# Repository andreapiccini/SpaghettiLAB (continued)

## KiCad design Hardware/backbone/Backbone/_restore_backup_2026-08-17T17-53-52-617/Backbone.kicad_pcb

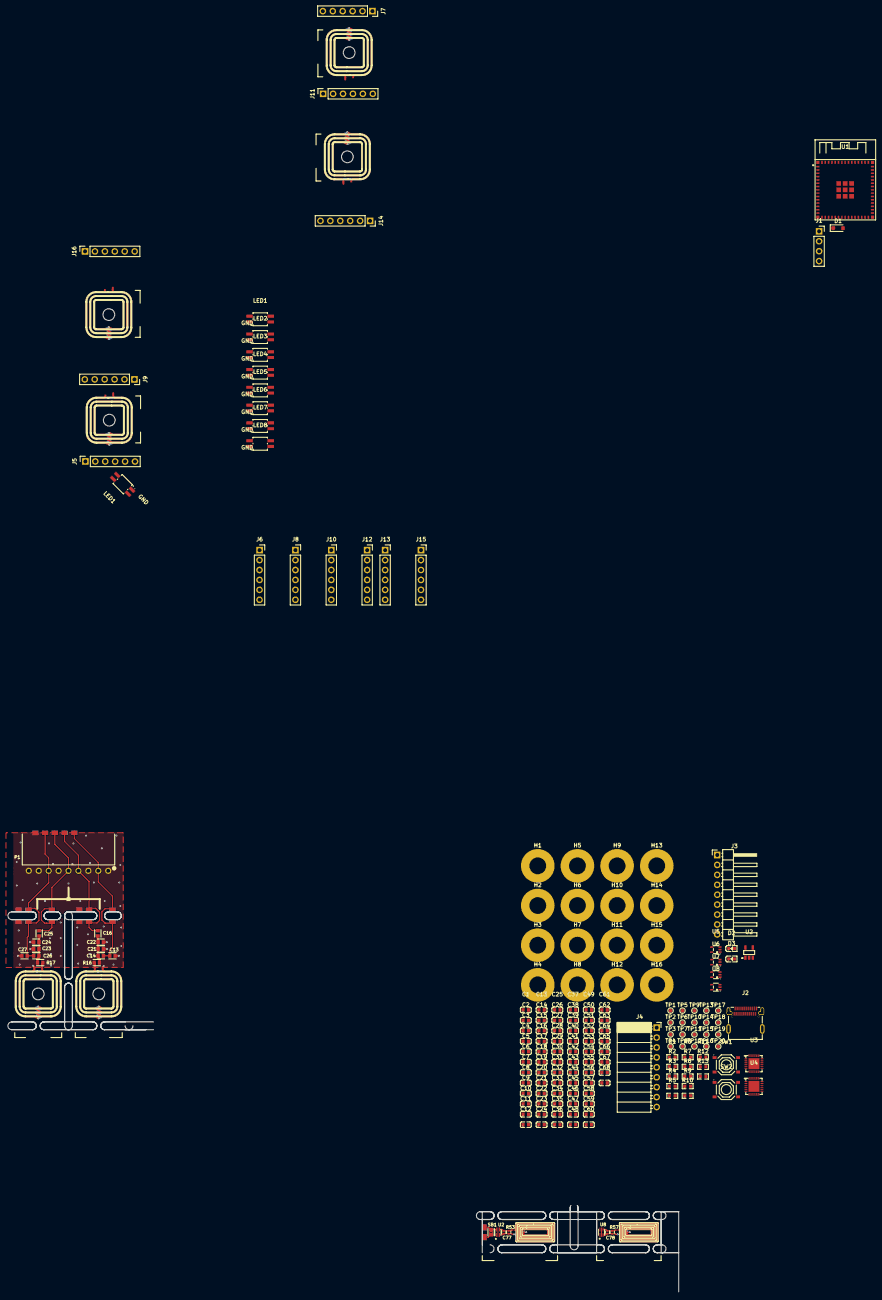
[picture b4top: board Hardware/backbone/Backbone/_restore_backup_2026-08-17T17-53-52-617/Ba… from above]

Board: 2 copper layers, 179 parts (0 on the bottom side), 118 nets.

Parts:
C1, C2, C9, C10, C25, C26#2, C39, C40, C41, C42, C47, C48, C53, C54, C67, C68: 100nF; C0603
C3, C8: 1uF; C0603
C4, C5, C6, C7, C56, C59, C62, C65: 10pF; C0603
C11, C12, C15, C16, C17, C18, C23#2, C24#2, C31, C32, C33, C34: 10nF; C0603
C13, C14, C19, C20, C21#2, C22#2, C35, C36: 2.2uF/10V; C0603
C13#2, C27: 150pF; 0603
C14#2, C26: 10pF; 0603
C16#2, C25#2: 39pF 2%; 0603
C21, C24: 220pF; 0603
C22, C23: 18pF 2%; 0603
C27#2, C28, C37, C38: 1uF/10V; C0603
C29, C30: 4.7uF/10V; C0603
C43, C44, C45, C46: 220pF 1%; C0603
C49, C50, C51, C52: 33pF 2%; C0603
C55, C58, C63, C66: 240pF; C0603
C57, C60, C61, C64: 150pF; C0603
C77: 33pF; 0402
C78: 6.8pF; 0402
D1: D_Schottky; D_SOD-323_HandSoldering
D2, D3: LED; LED0603-RD
H1, H2, H3, H4, H5, H6, H7, H8, H9, H10, H11, H12, H13, H14, H15, H16: Magnet; MountingHole_4.3mm_M4_Pad
J1: PROG; PinSocket_1x04_P2.54mm_Vertical
J2: USB_C_Receptacle_USB2.0_14P; USB-C-SMD_TYPEC-324G-BCP24
J3: EXP_MALE; PinHeader_1x09_P2.54mm_Horizontal
J4: EXP_FEMALE; PinSocket_1x09_P2.54mm_Horizontal
J5, J6, J7, J8, J9, J10, J11, J12, J13, J14, J15, J16: Conn_01x06_Socket; PinSocket_1x06_P2.54mm_Vertical
LED1, LED1#2, LED2, LED3, LED4, LED5, LED6, LED7, LED8: SK6812MINI-E; LED-SMD_4P-L3.2-W2.8-LS5.9_SK6812MINI-E
NT_C7_1, NT_C7_2: Net-Tie-Width-0.50mm; Net-Tie-WIDTH-0.50mm
NT_TAG1, NT_TAG2: Net-Tie-Width-0.10mm; Net-Tie-WIDTH-0.10mm
P1: SSW-109-02-G-S-RA; SAMTEC-SSW-1X9PTS-RA-THROUGH-HOLE
R1: 4.7k; R0603
R2, R3: 33R; R0603
R4, R5: 10k; R0603
R6, R7: 5.1k; R0603
R8, R9: 330R; R0603
R10, R11, R12, R13: 1R5; R0603
R16, R17: 1R5; 0603
R53, R57: TBD; 0402
SB1: SB 0603; STRAP-FORMAT-0603-OUVERT
SW1: RESET; SW-SMD_4P-L5.1-W5.1-P3.70-LS6.5-TL_H1.5
SW2: BOOT; SW-SMD_4P-L5.1-W5.1-P3.70-LS6.5-TL_H1.5
TP1, TP2, TP3, TP4, TP5, TP6, TP7, TP8, TP9, TP10, TP11, TP12: SMD/0.6mm; TestPoint_Pad_D1.0mm
TP13, TP14, TP15, TP16, TP17, TP18, TP19, TP20: SMD/0.8mm; TestPoint_Pad_D1.0mm
U1: ESP32-S3-MINI-1; BULETM-SMD_ESP32-S3-MINI-1-N8
U2: AP2112K-3.3TRG1; SOT-25-5_L2.9-W1.6-P0.95-LS2.8-BL
U2#2: ST25TV02KC-TFH3; ST-UFDFPN5-Pas=0.4-PKG-1.7x1.4
U3, U4: ST25R200; QFN-24_L4.0-W4.0-P0.50-TL-EP2.8
U5, U6, U7, U8#2: SN74AHCT1G14DCKR; SOT-353_L2.2-W1.4-P0.65-LS2.4-BR
U8: ST25TN01KAFH5; ST-UFDFPN5-Pas=0.4-PKG-1.7x1.4

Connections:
5V: C8.2, C25.2, C26#2.2 (2_2), C37.2, C38.2, C39.2, C40.2, C41.2, C42.2, C47.2, C48.2, C53.2, C54.2, C67.2, C68.2, D1.1 (K), J3.2, J4.8, J13.6, J14.6, J15.6, J16.6, LED1.3 (VDD), LED2.3 (VDD), LED3.3 (VDD), LED4.3 (VDD), LED5.3 (VDD), LED6.3 (VDD), LED7.3 (VDD), LED8.3 (VDD), R9.1, U2.1 (VIN), U2.3 (EN), U5.5 (VCC), U6.5 (VCC), U7.5 (VCC), U8#2.5 (VCC)
/AGD: C27#2.2, C28.2, C33.2, C34.2, U3.15 (AGD), U4.15 (AGD)
/BAY0: U1.19 (IO15), U6.2 (A)
/BAY1: U1.20 (IO16), U7.2 (A)
/BAY2: U1.21 (IO17), U5.2 (A)
/BAY3: U1.22 (IO18), U8#2.2 (A)
/RFI1_25R200: C56.1, C57.2, C59.1, C60.2, U3.16 (RFI1), U4.16 (RFI1)
/RFI2_25R200: C61.1, C62.2, C64.1, C65.2, U3.17 (RFI2), U4.17 (RFI2)
/RFO1_25R200: TP18.1 (1_1), TP20.1 (1_1), U3.9 (RFO1), U4.9 (RFO1)
/RFO1_C7_ANT: C44.1, C46.1, C49.1, C50.1
/RFO2_25R200: TP17.1 (1_1), TP19.1 (1_1), U3.10 (RFO2), U4.10 (RFO2)
/RFO2_C7_ANT: C43.2, C45.2, C51.1, C52.1
/TAD1_200: TP13.1 (1_1), TP14.1 (1_1), U3.13 (TAD1), U4.13 (TAD1)
/TAD2_200: TP15.1 (1_1), TP16.1 (1_1), U3.12 (TDA2), U4.12 (TDA2)
/USB_DM: R3.1, U1.23 (USB_D-)
/USB_DP: R2.1, U1.24 (USB_D+)
/VDD_A: C17.2, C18.2, C21#2.2, C22#2.2, U3.14 (VDD_A), U4.14 (VDD_A)
/VDD_AM: C15.2, C16.2, C19.2, C20.2, U3.6 (VDD_AM), U4.6 (VDD_AM)
/VDD_D: C11.2, C12.2, C13.2, C14.2, U3.5 (VDD_D), U4.5 (VDD_D)
/VDD_DR: C31.2, C32.2, C35.2, C36.2, U3.8 (VDD_DR), U4.8 (VDD_DR)
/XTI: C4.2, C6.2, U3.19 (XTI), U4.19 (XTI)
/XTO: C5.2, C7.2, U3.20 (XTO), U4.20 (XTO)
GND: C1.1, C2.1, C3.1, C4.1, C5.1, C6.1, C7.1, C8.1, C9.1, C10.1, C11.1, C12.1, C13.1, C14.1, C15.1, C16.1, C17.1, C18.1, C19.1, C20.1, C21#2.1, C22#2.1, C23#2.1, C24#2.1, C25.1, C27#2.1, C28.1, C29.1, C30.1, C31.1, C32.1, C33.1, C34.1, C35.1, C36.1, C37.1, C38.1, C39.1, C40.1, C41.1, C42.1, C43.1, C44.2, C45.1, C46.2, C47.1, C48.1, C53.1, C54.1, C55.2, C57.1, C58.2, C60.1, C61.2, C63.1, C64.2, C66.1, C67.1, C68.1, D2.1 (K), D3.1 (K), J1.4, J2.A1 (GND), J2.A12 (GND), J2.B1 (GND), J2.B12 (GND), J3.9, J4.1, J13.1, J14.1, J15.1, J16.1, LED1.1 (GND), LED2.1 (GND), LED3.1 (GND), LED4.1 (GND), LED5.1 (GND), LED6.1 (GND), LED7.1 (GND), LED8.1 (GND), R6.1, R7.1, SW1.1, SW2.1, U1.1 (GND), U1.2 (GND), U1.42 (GND), U1.43 (GND), U1.46 (GND), U1.47 (GND), U1.48 (GND), U1.49 (GND), U1.50 (GND), U1.51 (GND), U1.52 (GND), U1.53 (GND), U1.54 (GND), U1.55 (GND), U1.56 (GND), U1.57 (GND), U1.58 (GND), U1.59 (GND), U1.60 (GND), U2.2 (GND), U3.4 (GND_D), U3.11 (GND_DR), U3.18 (GND_A), U3.25 (GND(EP)), U4.4 (GND_D), U4.11 (GND_DR), U4.18 (GND_A), U4.25 (GND(EP)), U5.3 (GND), U6.3 (GND), U7.3 (GND), U8#2.3 (GND)
GND_HUB: C13#2.2, C21.1, C22.1, C23.2, C24.2, C27.1, NT_C7_1.1, NT_C7_2.1, P1.1, P1.3, P1.6, P1.8, P1.9
IO1: J16.5, U1.5 (IO1)
IO2: J16.4, U1.6 (IO2)
IO3: J16.3, U1.7 (IO3)
IO4: J16.2, U1.8 (IO4)
IO5: J15.5, U1.9 (IO5)
IO6: J15.4, U1.10 (IO6)
IO7: J15.3, U1.11 (IO7)
IO8: J15.2, U1.12 (IO8)
IO9: J14.5, U1.13 (IO9)
IO10: J14.4, U1.14 (IO10)
IO11: J14.3, U1.15 (IO11)
IO12: J14.2, U1.16 (IO12)
IO13: J13.5, U1.17 (IO13)
IO14: J13.4, U1.18 (IO14)
IO21: J13.3, U1.25 (IO21)
IO26: J13.2, U1.26 (IO26)
IO33: R5.2, TP6.1 (1_1), U1.28 (IO33), U4.22 (BSS)
IO34: TP11.1 (1_1), TP12.1 (1_1), U1.29 (IO34), U3.2 (MISO), U4.2 (MISO)
IO35: TP7.1 (1_1), U1.31 (IO35), U3.1 (IRQ)
IO36: TP3.1 (1_1), TP4.1 (1_1), U1.32 (IO36), U3.24 (SCLK), U4.24 (SCLK)
IO37: TP9.1 (1_1), TP10.1 (1_1), U1.33 (IO37), U3.23 (MOSI), U4.23 (MOSI)
IO38: R4.2, TP5.1 (1_1), U1.34 (IO38), U3.22 (BSS)
IO39: TP1.1 (1_1), TP2.1 (1_1), U1.35 (IO39), U3.21 (RESET), U4.21 (RESET)
IO40: TP8.1 (1_1), U1.36 (IO40), U4.1 (IRQ)
IO41: J3.3, J4.7, U1.37 (IO41)
IO42: J3.4, J4.6, U1.38 (IO42)
IO45: J3.5, J4.5, U1.41 (IO45)
IO46: J3.6, J4.4, U1.44 (IO46)
IO47: J3.7, J4.3, U1.27 (IO47)
IO48: J3.8, J4.2, U1.30 (IO48)
unnamed: C49.2, C55.1, C56.2, R10.1
unnamed: C50.2, C58.1, C59.2, R11.1
unnamed: C51.2, C62.1, C63.2, R12.1
unnamed: C52.2, C65.1, C66.2, R13.1
unnamed: D2.2 (A), R8.2
unnamed: D3.2 (A), R9.2
unnamed: J1.2, U1.39 (TXD0)
unnamed: J1.3, U1.40 (RXD0)
unnamed: J2.A5 (CC1), R7.2
unnamed: J2.B5 (CC2), R6.2
unnamed: J2.A6 (D+), J2.B6 (D+), R2.2
unnamed: J2.A7 (D-), J2.B7 (D-), R3.2
unnamed: J5.1, J9.6
unnamed: J5.2, J9.5
unnamed: J5.3, J9.4
unnamed: J5.4, J9.3
unnamed: J5.5, J9.2
unnamed: J5.6, J9.1
unnamed: J6.6, J10.1
unnamed: J6.5, J10.2
unnamed: J6.4, J10.3
unnamed: J6.3, J10.4
unnamed: J6.2, J10.5
unnamed: J6.1, J10.6
unnamed: J7.6, J11.1
unnamed: J7.5, J11.2
unnamed: J7.4, J11.3
unnamed: J7.3, J11.4
unnamed: J7.2, J11.5
unnamed: J7.1, J11.6
unnamed: J8.6, J12.1
unnamed: J8.5, J12.2
unnamed: J8.4, J12.3
unnamed: J8.3, J12.4
unnamed: J8.2, J12.5
unnamed: J8.1, J12.6
unnamed: LED1.2 (DIN), U5.4 (Y)
unnamed: LED1.4 (DOUT), LED3.2 (DIN)
unnamed: LED2.2 (DIN), U6.4 (Y)
unnamed: LED2.4 (DOUT), LED4.2 (DIN)
unnamed: LED5.2 (DIN), U7.4 (Y)
unnamed: LED5.4 (DOUT), LED7.2 (DIN)
unnamed: LED6.2 (DIN), U8#2.4 (Y)
unnamed: LED6.4 (DOUT), LED8.2 (DIN)
unnamed: R1.2, SW1.2, U1.45 (EN)
unnamed: SW2.2, U1.4 (IO0)
unnamed: C23#2.2, C29.2, U3.7 (VDD)
unnamed: C24#2.2, C30.2, U4.7 (VDD)
NetC14_1: C14#2.1, C16#2.2, C21.2, C22.2, R16.1
NetC23_1: C23.1, C24.1, C25#2.2, C26.2, R17.1
NetC77_1: C77.1, NT_TAG1.1, R53.1, U2#2.4
NetC77_2: C77.2, NT_TAG1.2, R53.2, U2#2.3
NetC78_1: C78.1, NT_TAG2.1, R57.1, U8.4
NetC78_2: C78.2, NT_TAG2.2, R57.2, U8.3
NetNT_C7_1_2: NT_C7_1.2, R17.2
NetNT_C7_2_2: NT_C7_2.2, R16.2
NetSB1_1: SB1.1, U2#2.5
NetSB1_2: SB1.2, U2#2.1
RFI1_C7_ANT: C26.1, C27.2, P1.7
RFI2_C7_ANT: C13#2.1, C14#2.2, P1.2
RFO1_C7_ANT: C25#2.1, P1.5
RFO2_C7_ANT: C16#2.1, P1.4
VBUS: D1.2 (A), J2.A4 (VBUS), J2.A9 (VBUS), J2.B4 (VBUS), J2.B9 (VBUS)
VCORE: C1.2, C2.2, C3.2, C9.2, C10.2, J1.1, J3.1, J4.9, R1.1, R4.1, R5.1, R8.1, U1.3 (3V3), U2.5 (VOUT), U3.3 (VDD_IO), U4.3 (VDD_IO)

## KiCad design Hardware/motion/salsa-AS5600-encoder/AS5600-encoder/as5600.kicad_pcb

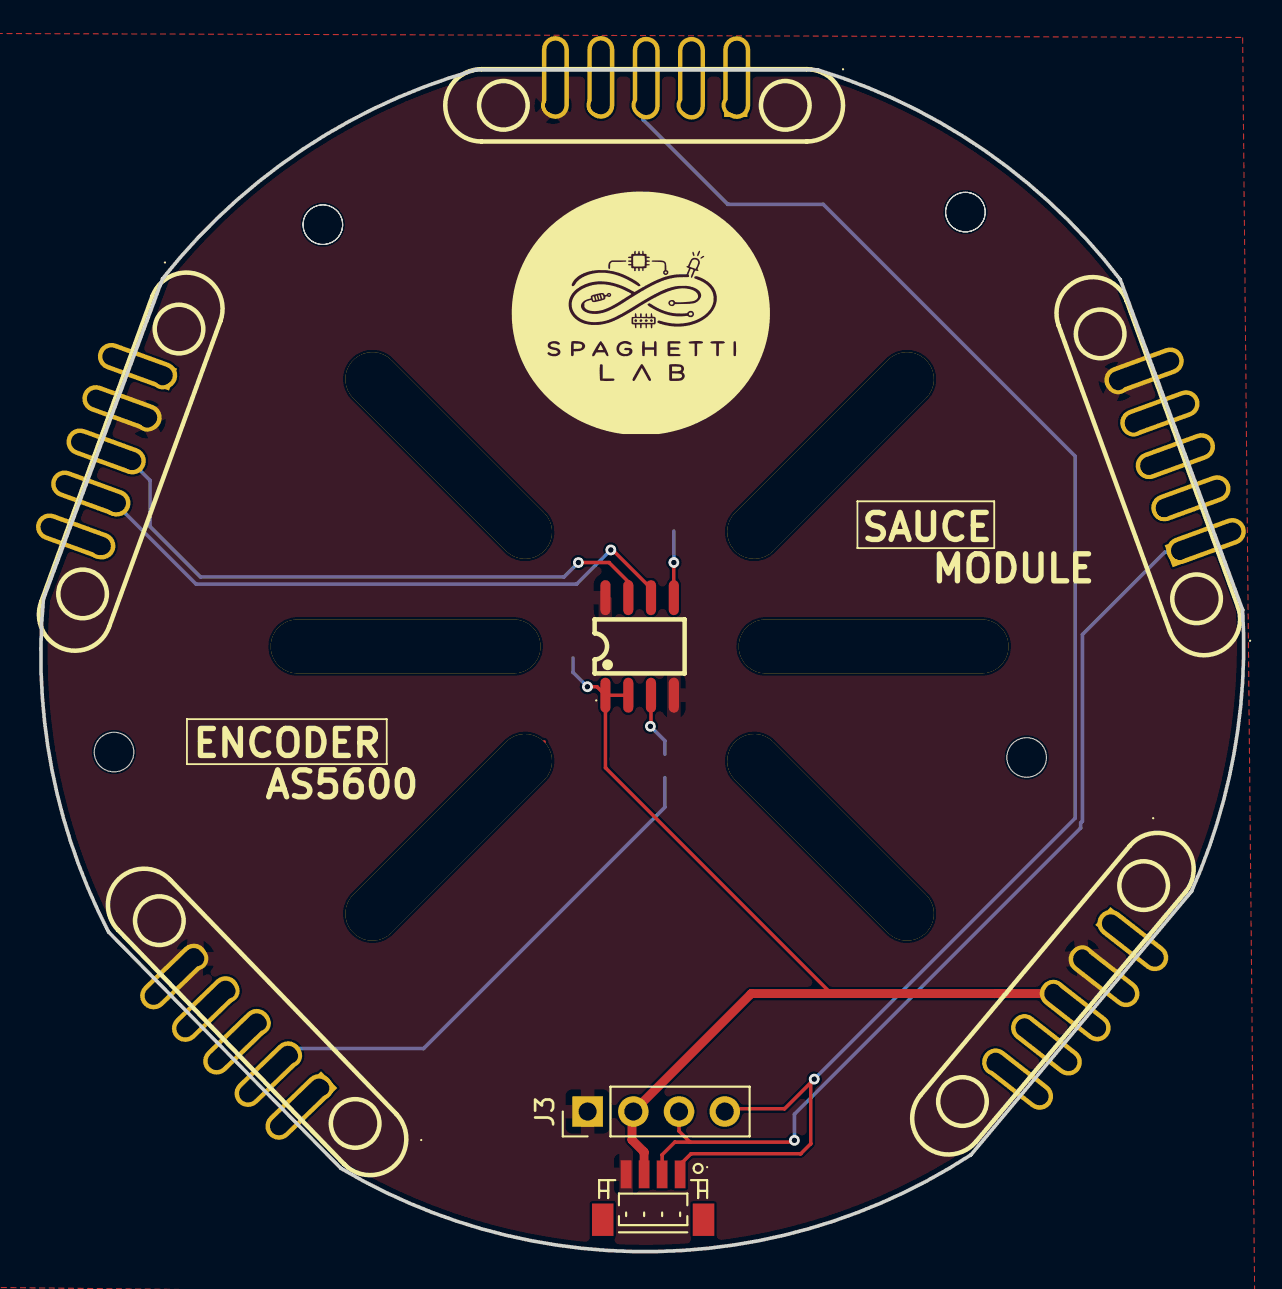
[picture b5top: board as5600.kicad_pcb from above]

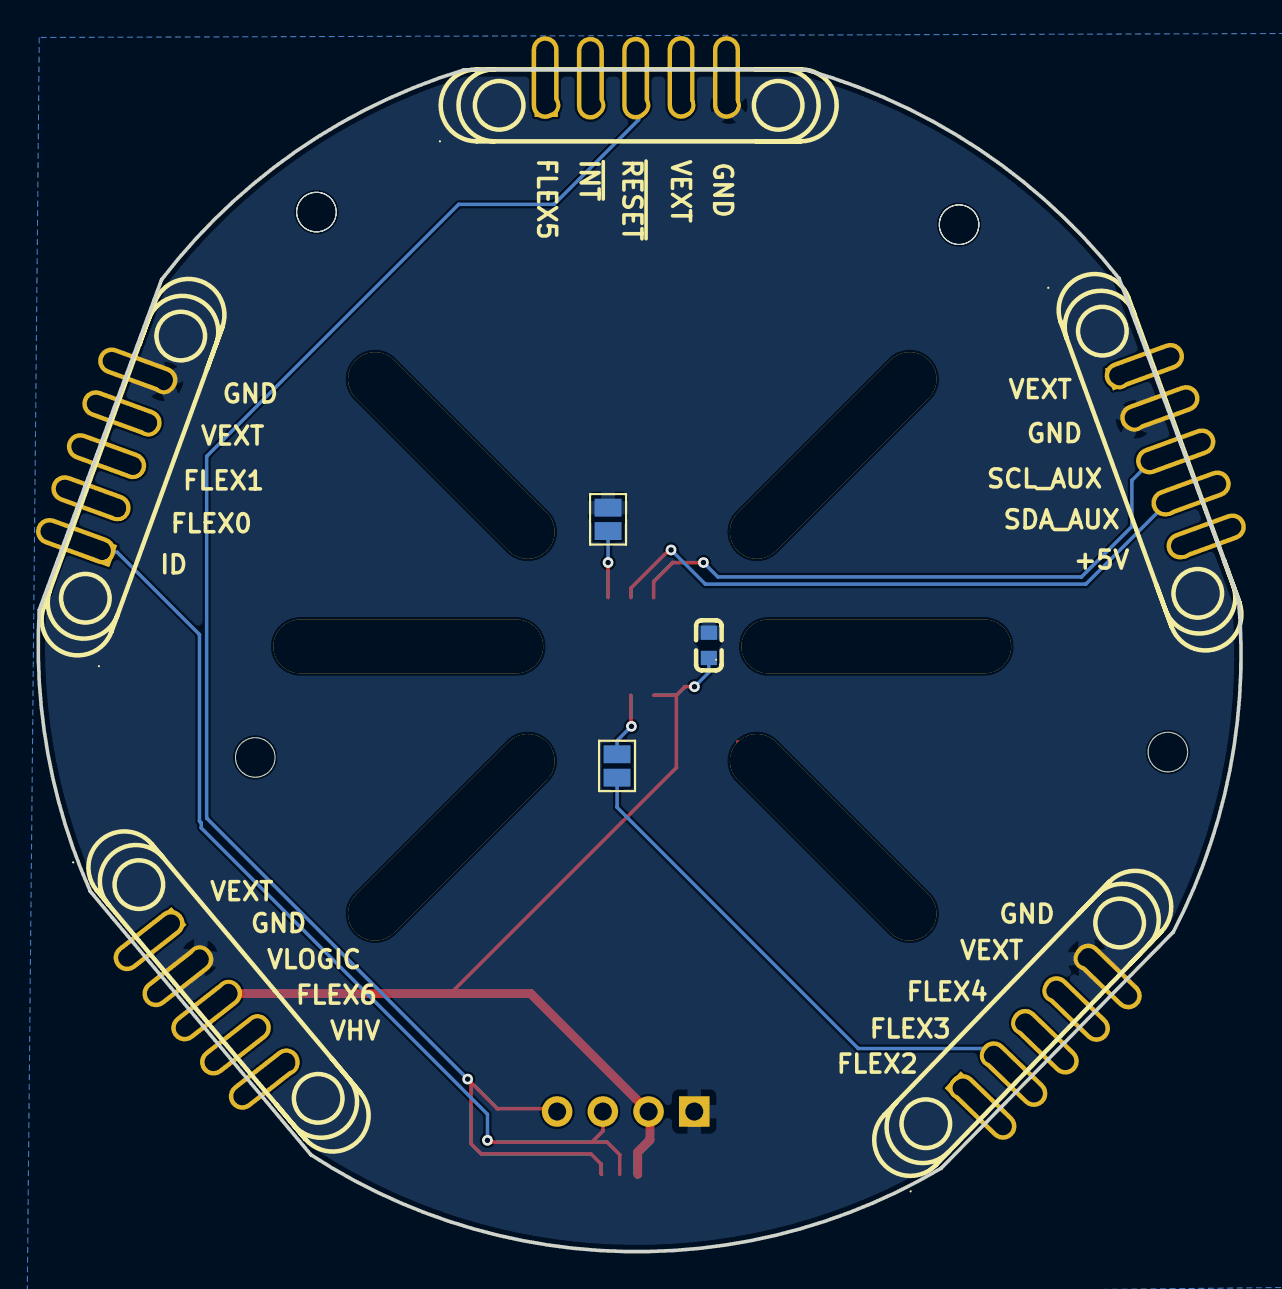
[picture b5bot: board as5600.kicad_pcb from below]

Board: 2 copper layers, 66.8 x 65.6 mm, 22 parts (8 on the bottom side), 19 nets.

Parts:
C1: 100nF 10V; C0603
CN7, CN8, CN9, CN10, CN11: PR5L4015-5P-C-F; CONN-TH_PR5L4015-5P-C-F
H1, H2, H3, H3#2, H4, H4#2: MountingHole; MountingHole_2.2mm_M2
J1: Conn_01x04_Socket; CONN-SMD_BM04B-SRSS-TB
J3: Conn_01x04_Pin; PinHeader_1x04_P2.54mm_Vertical
JP2, JP4: ENC_PGO; SolderJumper-2_P1.3mm_Open_Pad1.0x1.5mm
U1: AS5600-ASOT; SOIC-8_L5.0-W4.0-P1.27-LS6.0-BL
U35, U36, U37, U38, U39: PR5L5015-5P-C-H; CONN-TH_PR5L5015-5P-C-H

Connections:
5V: CN8.5, U35.5
+3.3V: C1.1, CN11.3, J1.3, J3.2, U1.1 (VDD5V), U1.2 (VDD3V3), U39.3
/FLEX0: CN10.2, U37.2
/FLEX1: CN10.3, U37.3
/FLEX2: CN7.1, U38.1
/FLEX3: CN7.2, JP4.2 (B), U38.2
/FLEX4: CN7.3, U38.3
/FLEX5: CN9.1, U36.1
/FLEX6: CN11.4, U39.4
/ID: CN10.1, J1.2, J3.3, U37.1
/~INT: CN9.2, U36.2
/~RESET: CN9.3, J1.1, J3.4, U36.3
ENC_AOUT: JP4.1 (A), U1.3 (OUT)
ENC_SCL: CN8.3, U1.7 (SCL), U35.3
ENC_SDA: CN8.4, U1.6 (SDA), U35.4
GND: C1.2, CN7.5, CN8.2, CN9.5, CN10.5, CN11.2, J1.4, J3.1, JP2.2 (B), U1.4 (GND), U1.8 (DIR), U35.2, U36.5, U37.5, U38.5, U39.2
unnamed: JP2.1 (A), U1.5 (PGO)
VEXT: CN7.4, CN8.1, CN9.4, CN10.4, CN11.1, U35.1, U36.4, U37.4, U38.4, U39.1
VHV: CN11.5, U39.5

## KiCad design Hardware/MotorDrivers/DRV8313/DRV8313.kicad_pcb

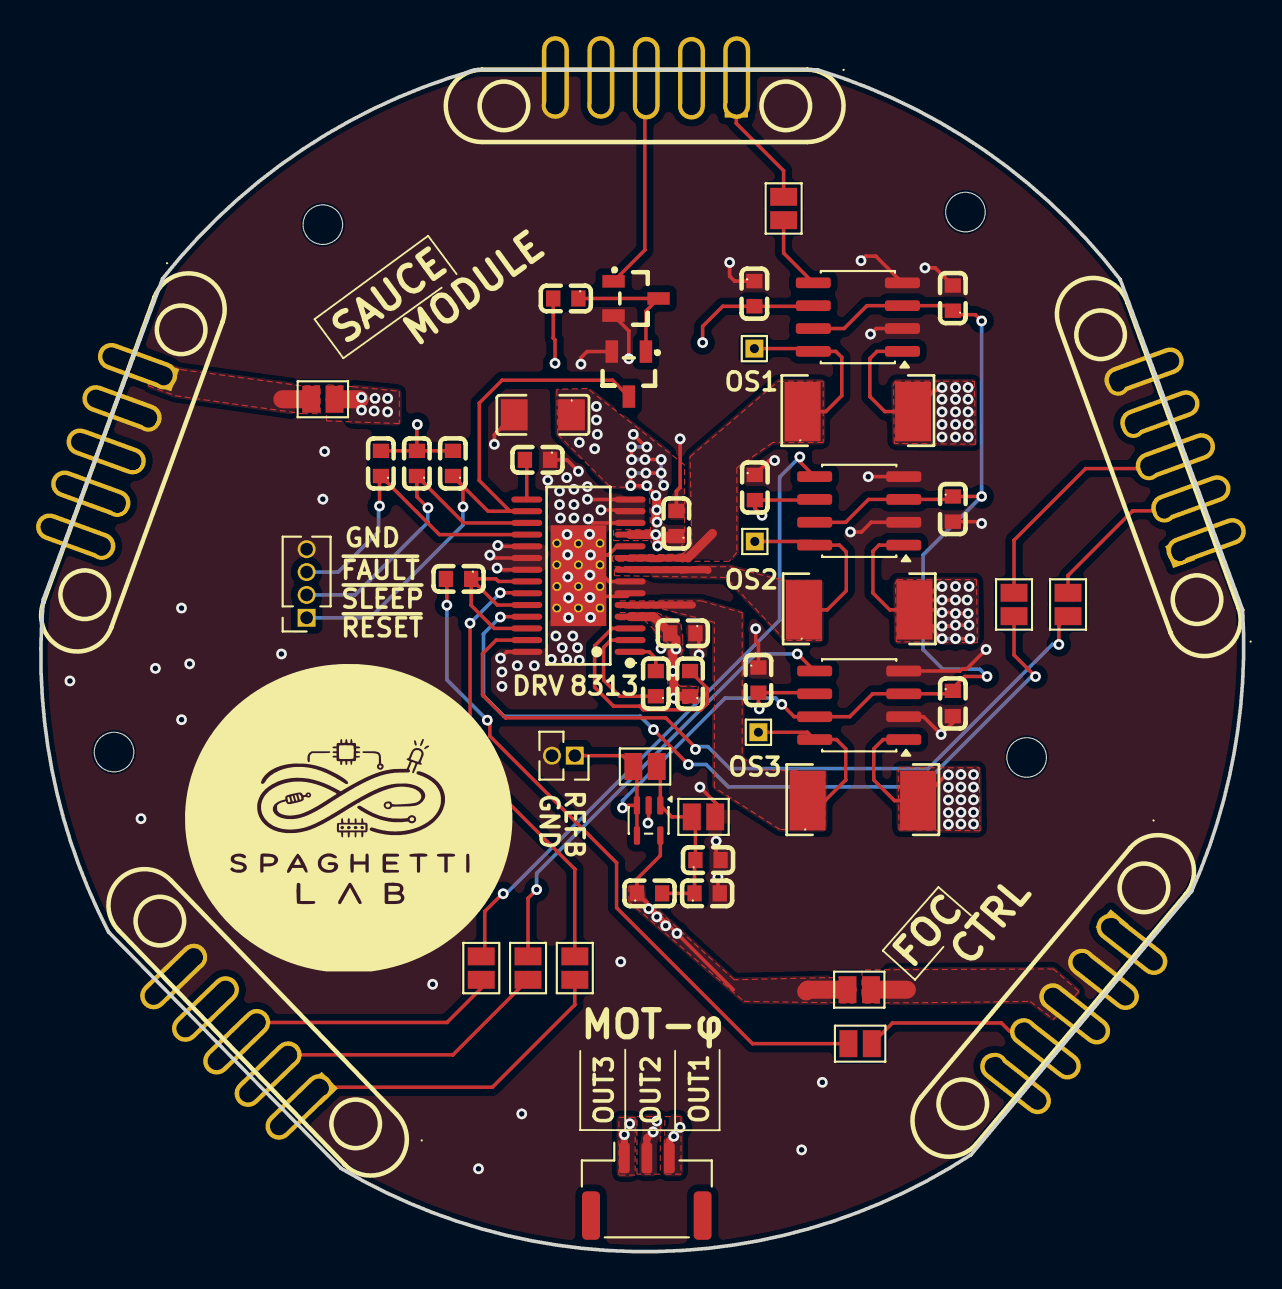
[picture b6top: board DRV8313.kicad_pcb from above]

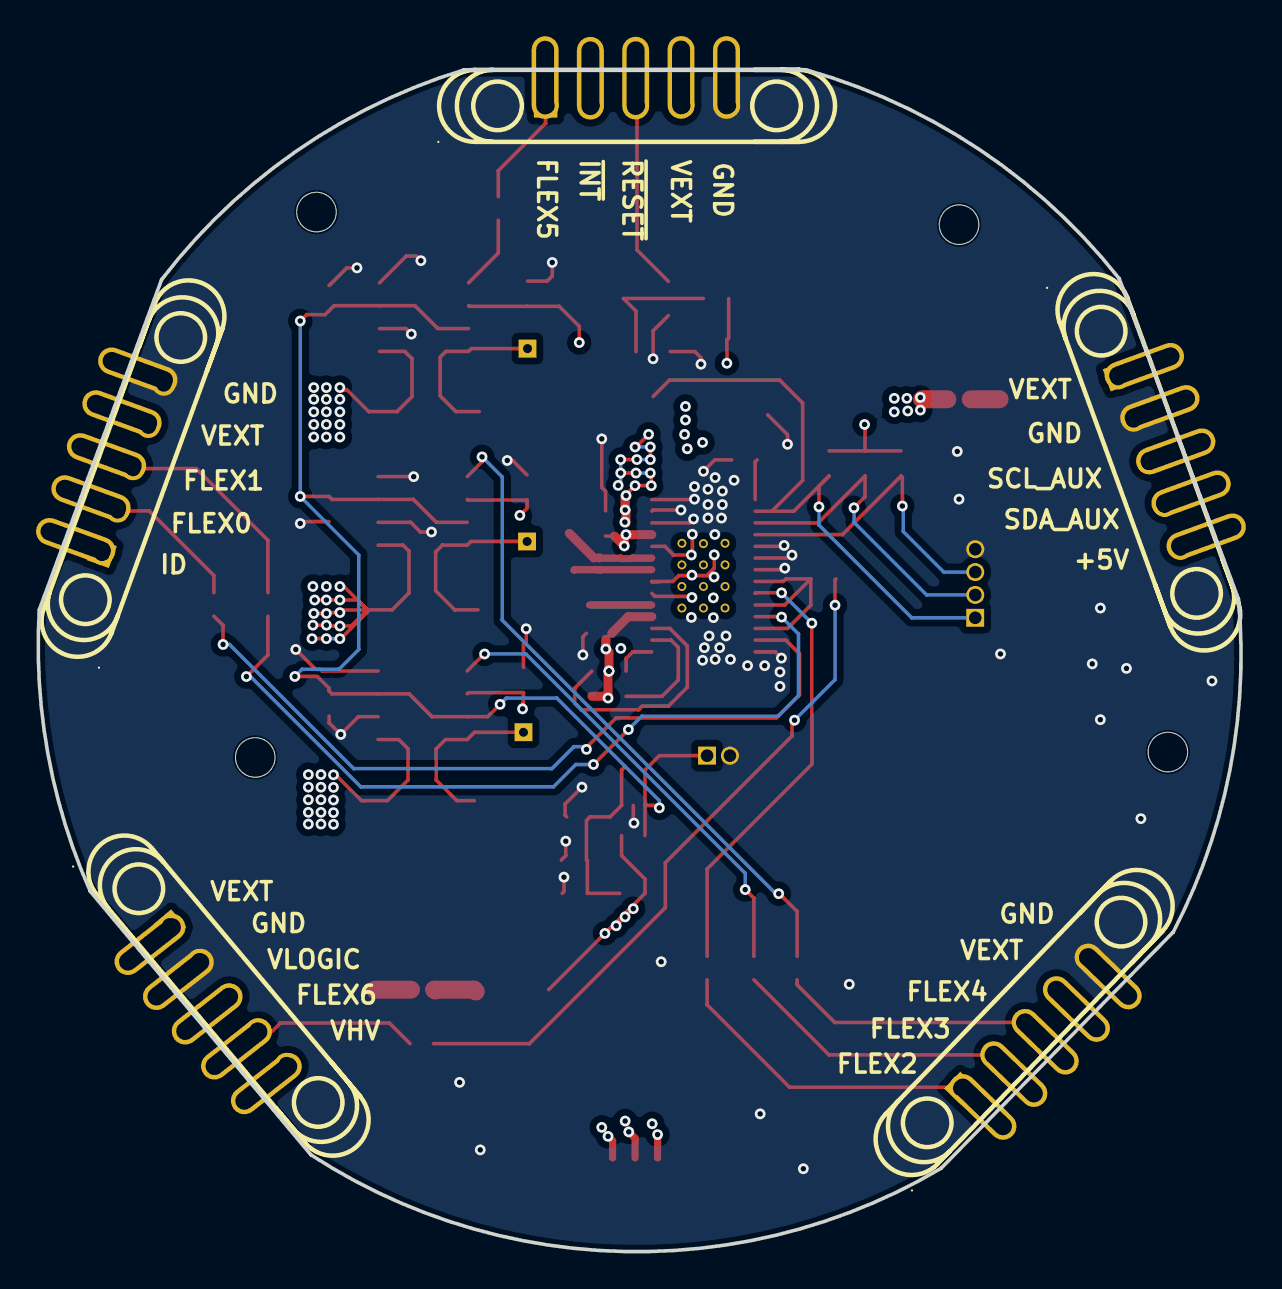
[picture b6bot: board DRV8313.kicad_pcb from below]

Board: 4 copper layers, 66.8 x 65.6 mm, 61 parts (5 on the bottom side), 43 nets.

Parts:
C1: 10nF; C0603
C2, C5, C6, C7, C8, C9, C11, C12, C13: 100nF; C0603
C3: 470nF; C0603
C4: 10uF; C1206
C10: 1uF; C0603
CN7, CN8, CN9, CN10, CN11: PR5L4015-5P-C-F; CONN-TH_PR5L4015-5P-C-F
H1, H2, H3, H4: MountingHole; MountingHole_2.2mm_M2
J1: Conn_01x04_Socket; PinSocket_1x04_P1.27mm_Vertical
J3: Conn_01x02_Socket; PinSocket_1x02_P1.27mm_Vertical
J4: Conn_01x03_Socket; JST_GH_SM03B-GHS-TB_1x03-1MP_P1.25mm_Horizontal
JP1, JP2: Jumper_2_Open; SolderJumper-2_P1.3mm_Open_Pad1.0x1.5mm
JP3, JP4, JP5, JP6, JP7, JP8, JP9, JP10, JP11: SolderJumper_2_Open; SolderJumper-2_P1.3mm_Open_Pad1.0x1.5mm
Q1, Q2: BSS123_C427379; SOT-23-3_L2.9-W1.5-P1.90-LS2.6-BR
R1, R2, R3, R4, R5, R10: 10k; C0603
R6, R7, R8: 10m; RES-SMD_L6.4-W3.2-R2512
R9: 1k; C0603
TP1, TP2, TP3: TestPoint_Flag; TestPoint_THTPad_1.0x1.0mm_Drill0.5mm
U1: MS8313; HTSSOP-28_L9.7-W4.4-P0.65-LS6.4-BL-EP
U2: TLV9001IDCK; SOT-353_SC-70-5
U5, U6, U7: INA241A2xD; SOIC-8_3.9x4.9mm_P1.27mm
U35, U36, U37, U38, U39: PR5L5015-5P-C-H; CONN-TH_PR5L5015-5P-C-H

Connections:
5V: CN8.5, U35.5
+3.3V: C7.2, C8.2, C9.2, JP4.2 (B), R1.1, R3.2, R4.2, R5.2, R10.2, U2.5 (V+), U5.6 (V+), U6.6 (V+), U7.6 (V+)
/FLEX0: CN10.2, JP8.1 (A), U37.2
/FLEX1: CN10.3, JP9.1 (A), U37.3
/FLEX2: CN7.1, JP10.1 (A), U38.1
/FLEX3: CN7.2, JP5.1 (A), U38.2
/FLEX4: CN7.3, JP6.1 (A), U38.3
/FLEX5: CN9.1, JP7.1 (A), U36.1
/FLEX6: CN11.4, JP11.1 (A), U39.4
/ID: CN10.1, U37.1
/OUT_SENSE1: R6.1, TP1.1 (1_1), U1.5 (OUT1), U5.8 (+)
/OUT_SENSE2: R7.1, TP2.1 (1_1), U1.8 (OUT2), U6.8 (+)
/OUT_SENSE3: R8.1, TP3.1 (1_1), U1.9 (OUT3), U7.8 (+)
/REF: C10.1, JP1.2 (B), JP2.1 (A), R1.2, R2.1, U2.1 (+)
/REF_B: C11.1, C12.1, C13.1, J3.1, JP2.2 (B), U2.3 (-), U2.4, U5.3 (REF2), U5.7 (REF1), U6.3 (REF2), U6.7 (REF1), U7.3 (REF2), U7.7 (REF1)
/SCL_AUX: CN8.3, U35.3
/SDA_AUX: CN8.4, U35.4
/~INT: CN9.2, U36.2
/~RESET: CN9.3, Q1.1 (G), U36.3
C_SENSE1: JP5.2 (B), U5.5
C_SENSE2: JP6.2 (B), U6.5
C_SENSE3: JP7.2 (B), U7.5
EN: JP11.2 (B), R9.2
GND: C3.1, C4.2, C5.2, C6.1, C7.1, C8.1, C9.1, C10.2, C11.2, C12.2, C13.2, CN7.5, CN8.2, CN9.5, CN10.5, CN11.2, J1.4, J3.2, JP1.1 (A), Q1.2 (S), Q2.2 (S), R2.2, U1.6 (PGND1), U1.7 (PGND2), U1.10 (PGND3), U1.12 (COMPP), U1.13 (COMPN), U1.14 (GND), U1.19 (nCOMP0), U1.20 (GND), U1.21 (NC), U1.28 (GND), U1.29 (EP), U2.2 (V-), U5.2 (GND), U5.4 (GND), U6.2 (GND), U6.4 (GND), U7.2 (GND), U7.4 (GND), U35.2, U36.5, U37.5, U38.5, U39.2
IN1: JP8.2 (B), U1.27 (IN1)
IN2: JP9.2 (B), U1.25 (IN2)
IN3: JP10.2 (B), U1.23 (IN3)
unnamed: Q1.3 (D), Q2.1 (G), R10.1
unnamed: C1.2, U1.1 (CP1)
unnamed: C1.1, U1.2 (CP2)
unnamed: R9.1, U1.22 (EN3), U1.24 (EN2), U1.26 (EN1)
unnamed: C2.2, U1.3 (VCP)
OUT1: J4.3, R6.2, U5.1 (-)
OUT2: J4.2, R7.2, U6.1 (-)
OUT3: J4.1, R8.2, U7.1 (-)
V3P3: C3.2, U1.15 (V3P3OUT)
VCC: C2.1, C4.1, C5.1, C6.2, JP3.2 (B), U1.4 (VM), U1.11 (VM)
VEXT: CN7.4, CN8.1, CN9.4, CN10.4, CN11.1, JP3.1 (A), U35.1, U36.4, U37.4, U38.4, U39.1
VHV: CN11.5, U39.5
VLOGIC: CN11.3, JP4.1 (A), U39.3
nFAULT: J1.3, R5.1, U1.18 (nFAULT)
nRESET: J1.1, Q2.3 (D), R3.1, U1.16 (nRESET)
nSLEEP: J1.2, R4.1, U1.17 (nSLEEP)

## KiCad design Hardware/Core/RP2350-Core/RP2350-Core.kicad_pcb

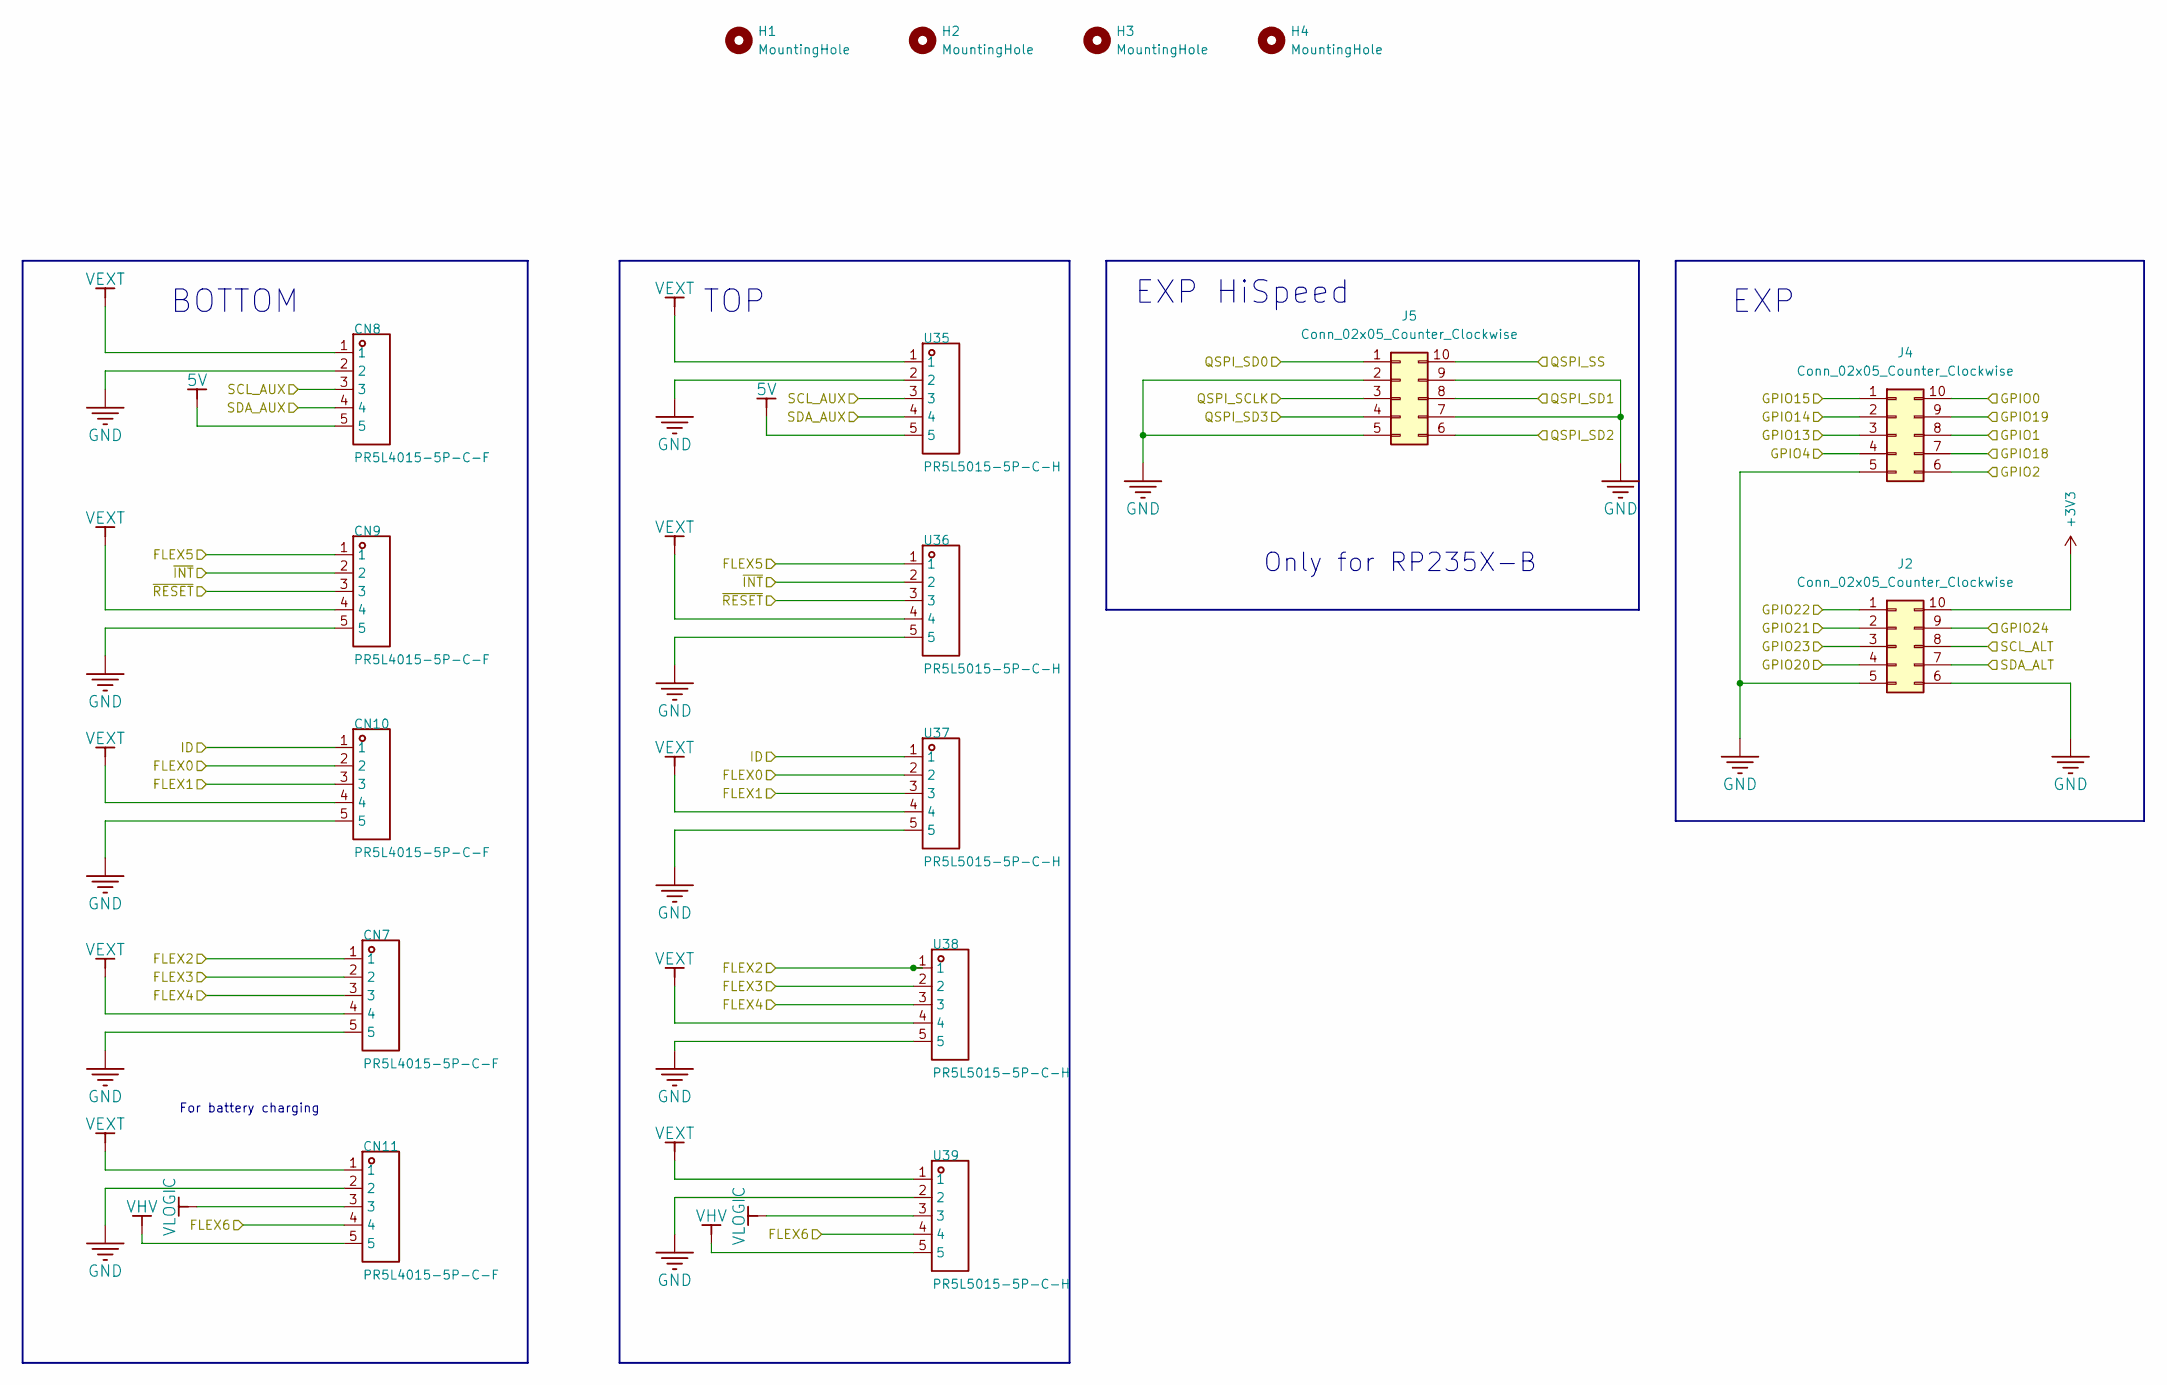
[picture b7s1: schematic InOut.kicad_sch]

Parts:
CN7, CN8, CN9, CN10, CN11: PR5L4015-5P-C-F; CONN-TH_PR5L4015-5P-C-F; Manufacturer Part PR5L4015-5P-C-F; LCSC Part Name 2.54-5P磁吸弹簧探针连接器母座POGOPIN适配PR5L5015-5P-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
H1, H2, H3, H4: MountingHole; MountingHole_2.2mm_M2
J2, J4, J5: Conn_02x05_Counter_Clockwise; PinSocket_2x05_P2.54mm_Vertical
U35, U36, U37, U38, U39: PR5L5015-5P-C-H; CONN-TH_PR5L5015-5P-C-H; Manufacturer Part PR5L5015-5P-C-H; LCSC Part Name 2.54-5P磁吸弹簧探针连接器公头POGOPIN适配PR5L4015-5P-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

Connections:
5V: CN8.5, U35.5
+3V3: J2.10; also elsewhere on the board
/InOut (page 4)/FLEX0: CN10.2, U37.2; also elsewhere on the board
/InOut (page 4)/FLEX1: CN10.3, U37.3; also elsewhere on the board
/InOut (page 4)/FLEX2: CN7.1, U38.1; also elsewhere on the board
/InOut (page 4)/FLEX3: CN7.2, U38.2; also elsewhere on the board
/InOut (page 4)/FLEX4: CN7.3, U38.3; also elsewhere on the board
/InOut (page 4)/FLEX5: CN9.1, U36.1; also elsewhere on the board
/InOut (page 4)/FLEX6: CN11.4, U39.4; also elsewhere on the board
/InOut (page 4)/GPIO0: J4.10; also elsewhere on the board
/InOut (page 4)/GPIO1: J4.8; also elsewhere on the board
/InOut (page 4)/GPIO2: J4.6; also elsewhere on the board
/InOut (page 4)/GPIO4: J4.4; also elsewhere on the board
/InOut (page 4)/GPIO13: J4.3; also elsewhere on the board
/InOut (page 4)/GPIO14: J4.2; also elsewhere on the board
/InOut (page 4)/GPIO15: J4.1; also elsewhere on the board
/InOut (page 4)/GPIO18: J4.7; also elsewhere on the board
/InOut (page 4)/GPIO19: J4.9; also elsewhere on the board
/InOut (page 4)/GPIO20: J2.4; also elsewhere on the board
/InOut (page 4)/GPIO21: J2.2; also elsewhere on the board
/InOut (page 4)/GPIO22: J2.1; also elsewhere on the board
/InOut (page 4)/GPIO23: J2.3; also elsewhere on the board
/InOut (page 4)/GPIO24: J2.9; also elsewhere on the board
/InOut (page 4)/ID: CN10.1, U37.1; also elsewhere on the board
/InOut (page 4)/QSPI_SCLK: J5.3; also elsewhere on the board
/InOut (page 4)/QSPI_SD0: J5.1; also elsewhere on the board
/InOut (page 4)/QSPI_SD1: J5.8; also elsewhere on the board
/InOut (page 4)/QSPI_SD2: J5.6; also elsewhere on the board
/InOut (page 4)/QSPI_SD3: J5.4; also elsewhere on the board
/InOut (page 4)/QSPI_SS: J5.10; also elsewhere on the board
/InOut (page 4)/SCL_ALT: J2.8; also elsewhere on the board
/InOut (page 4)/SCL_AUX: CN8.3, U35.3; also elsewhere on the board
/InOut (page 4)/SDA_ALT: J2.7; also elsewhere on the board
/InOut (page 4)/SDA_AUX: CN8.4, U35.4; also elsewhere on the board
/InOut (page 4)/~INT: CN9.2, U36.2; also elsewhere on the board
/InOut (page 4)/~RESET: CN9.3, U36.3; also elsewhere on the board
GND: CN7.5, CN8.2, CN9.5, CN10.5, CN11.2, J2.5, J2.6, J4.5, J5.2, J5.5, J5.7, J5.9, U35.2, U36.5, U37.5, U38.5, U39.2; also elsewhere on the board
VEXT: CN7.4, CN8.1, CN9.4, CN10.4, CN11.1, U35.1, U36.4, U37.4, U38.4, U39.1
VHV: CN11.5, U39.5
VLOGIC: CN11.3, U39.3; also elsewhere on the board

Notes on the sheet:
EXP
BOTTOM
TOP
EXP HiSpeed
Only for RP235X-B
For battery charging
